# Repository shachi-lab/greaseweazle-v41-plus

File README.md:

# Shachi-lab Greaseweazle V4.1 Plus Board

[🇯🇵 日本語版はこちら](README_ja.md)

This repository contains KiCad design data for a Greaseweazle V4.1 based compatible board created by Shachi-lab.

This board is based on Greaseweazle V4.1, with a few small modifications to make it easier to use with 5.25-inch FDDs and PC-98 style FDD setups.

For convenience, this board is referred to as **V4.1 Plus** in this repository.

**V4.1 Plus is not an official Greaseweazle product name.**

---

## About Greaseweazle

Greaseweazle is an open-source USB floppy interface for reading and writing floppy disks using standard PC floppy disk drives.

Unlike ordinary USB floppy drives, Greaseweazle can access floppy disks at a lower level.  
It can capture and write magnetic flux transitions, which makes it useful for handling disk formats that are not supported by standard USB floppy drives.

For firmware, host tools, usage, and detailed documentation, please refer to the original Greaseweazle project.

* Original Greaseweazle project  
  https://github.com/keirf/greaseweazle

* Greaseweazle Wiki  
  https://github.com/keirf/greaseweazle/wiki

---

## About this repository

This repository provides only the KiCad design data for the Shachi-lab Greaseweazle compatible board.

Firmware, host tools, and usage instructions are not included in this repository.  
This board is a clone-based compatible board, so basic usage follows the original Greaseweazle documentation.

---

## KiCad version

This board design was created with **KiCad 10.0**.

Older versions of KiCad may not open the project correctly.

---

## Board overview

This board is based on Greaseweazle V4.1.

The circuit is close to the original Greaseweazle V4.1 design.  
The board outline, mounting holes, connectors, pin headers, and LED positions are kept as close as possible to the original V4.1 board.

Some parts were changed to make the board easier to hand-assemble and easier to use with 5.25-inch FDDs and PC-98 related FDD setups.

---

## Main differences from the original V4.1 board

* 2-layer PCB
  * The original Greaseweazle V4.1 board is a 4-layer PCB
* SMT parts are mainly 0603 / 1608 size
  * The original board uses 0402 parts
  * This change makes hand assembly easier
* Additional pin headers for PC-98 FDD use
  * These headers are intended for cutting or controlling specific signals
* Additional +12V output path for 5.25-inch FDDs
  * Allows +12V from a common AC adapter to be supplied to a Berg connector

---

## Current status

The board has been tested with a 3.5-inch FDD and a standard DOS/Windows 1.44MB floppy disk.

Confirmed so far:

* Greaseweazle Firmware 1.6 programming
* USB connection on Windows 11
* Recognition with `gw info`
* 3.5-inch FDD connection
* Reading a DOS/Windows 1.44MB floppy disk
* Creating an IMG file using the `ibm.1440` profile
* Opening the IMG file with 7-Zip

The FDD used for this test was `SONY MPF920`.

---

## Not yet confirmed

The following items are still under test.

* Reading PC-98 5.25-inch floppy disks
* Stable operation with 5.25-inch FDDs
* 300rpm / 360rpm related behavior
* DENS signal behavior
* Compatibility with various FDD models

---

## Firmware and usage

Firmware, host tools, and usage follow the original Greaseweazle documentation.

This repository does not include Greaseweazle firmware or host tools.

For this board, the AT32F4 HEX file was used.

Example:

```text
greaseweazle-firmware-at32f4-1.6.hex
```

In my test environment, `gw info` showed the following result.

```text
Host Tools: 1.23
Device:
  Port:     COM7
  Model:    Greaseweazle V4.1
  MCU:      AT32F403A, 216MHz, 224kB SRAM
  Firmware: 1.6
  Serial:   GW053C11222847000007E0A413
  USB:      Full Speed (12 Mbit/s), 128kB Buffer
```

The `Greaseweazle V4.1` model name shown here is returned by the Greaseweazle firmware.  
It does not mean that this board is an official Greaseweazle V4.1 board.

---

## Notes

This is a self-made Greaseweazle compatible board created by Shachi-lab.  
It is not an official Greaseweazle product.

If you build this board, please check the KiCad design data and circuit carefully.  
Use it at your own risk.

Old floppy disks and FDDs may have various mechanical and media-related issues.  
Damaged or dirty floppy disks may cause unstable reading behavior or may contaminate the FDD head.

---

## Related article

Related articles are available on the Shachi-lab blog.

Please note that the blog articles are written in Japanese.

- Greaseweazle category  
  https://blog.shachi-lab.com/category/microcontroller/greaseweazle/
---

## License

This board is based on the original Greaseweazle project by Keir Fraser.

The KiCad design data in this repository is released with respect for the original Greaseweazle project and under the license terms of the original project.

Please refer to the original Greaseweazle repository for license details.

* https://github.com/keirf/greaseweazle

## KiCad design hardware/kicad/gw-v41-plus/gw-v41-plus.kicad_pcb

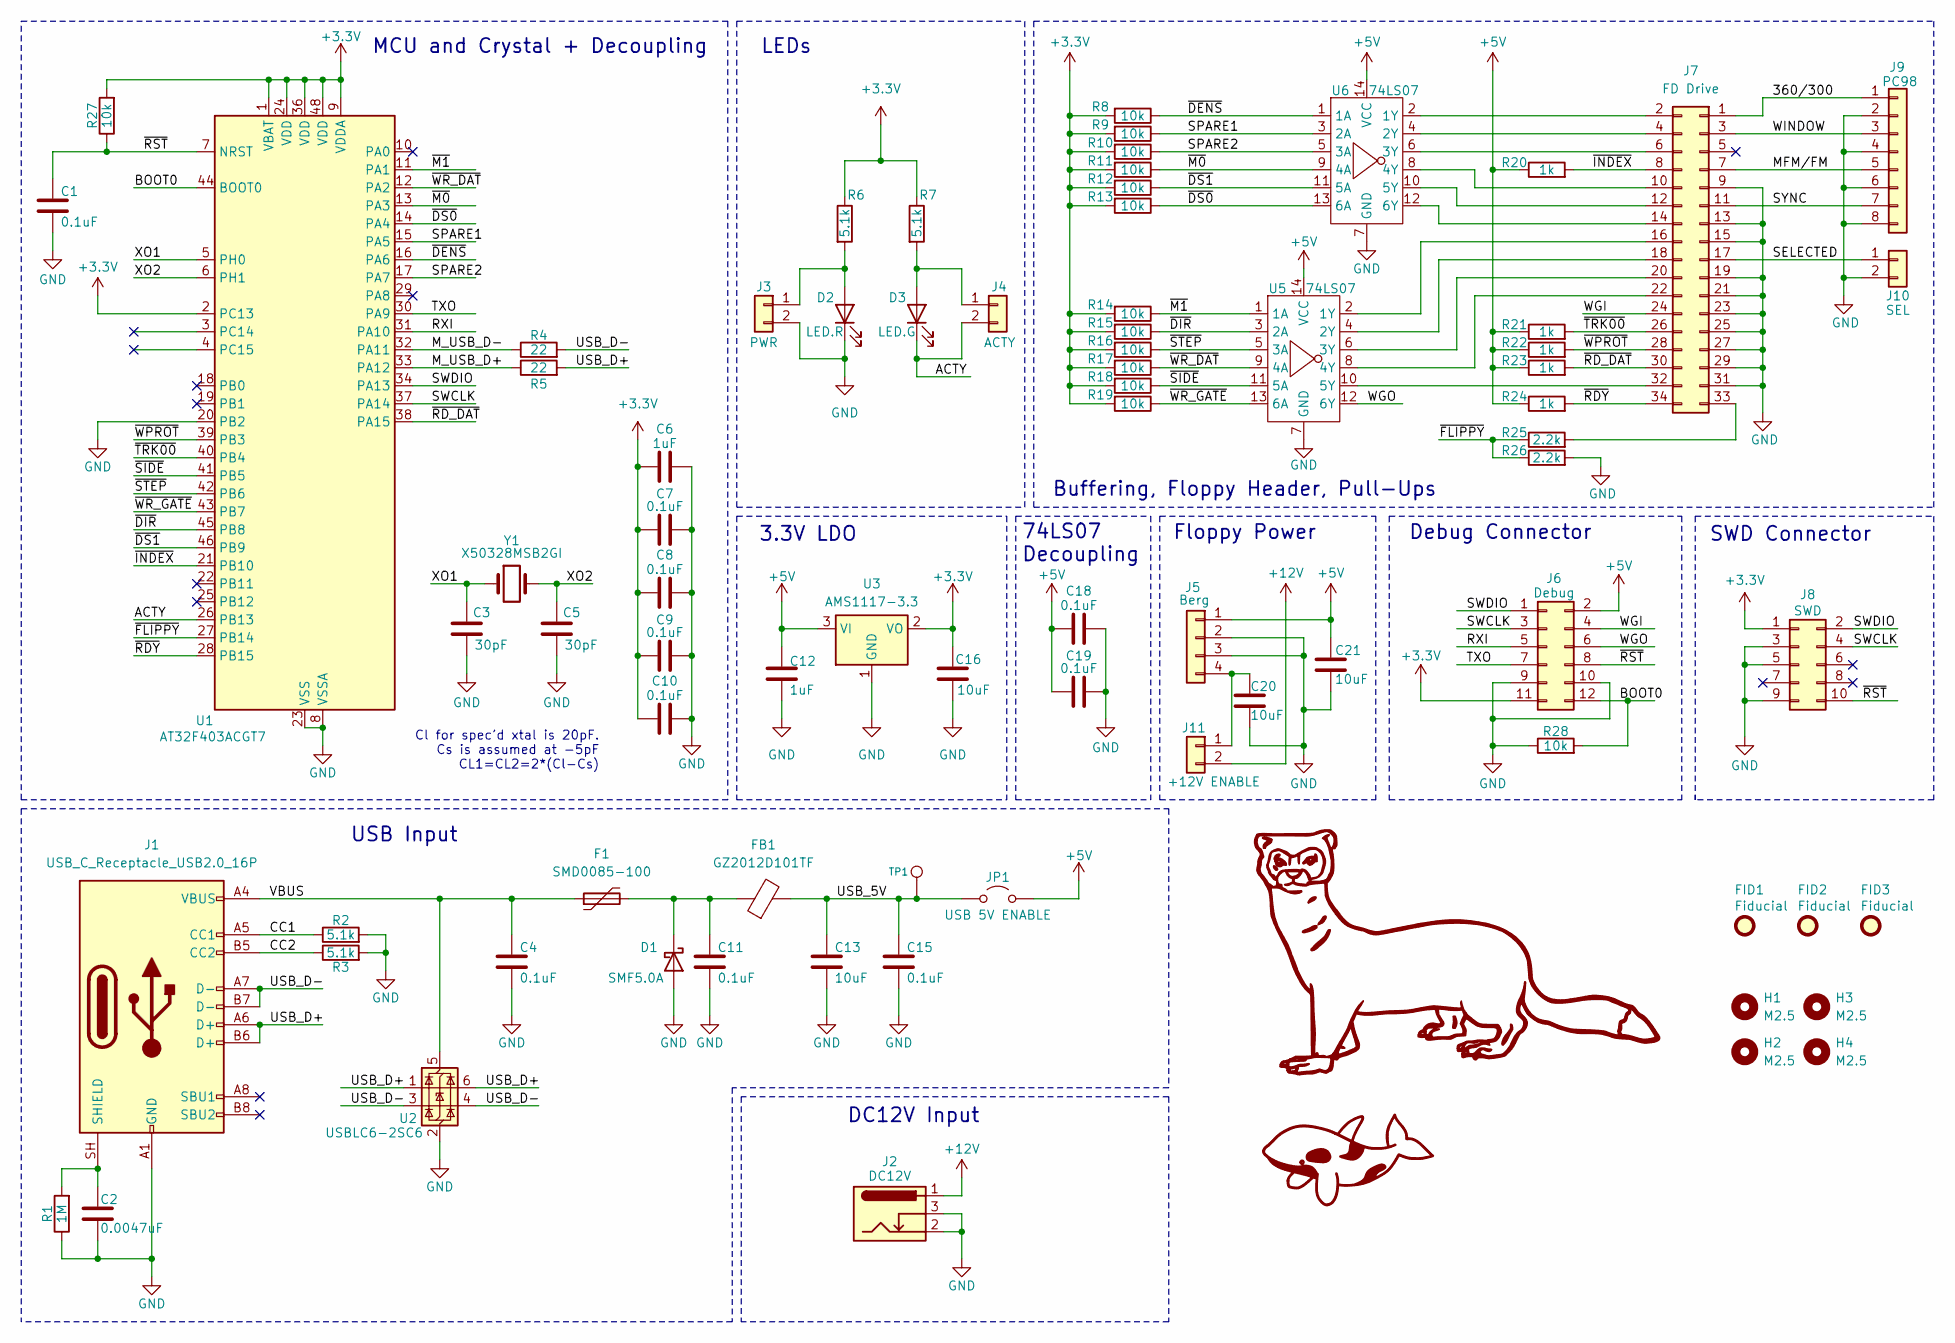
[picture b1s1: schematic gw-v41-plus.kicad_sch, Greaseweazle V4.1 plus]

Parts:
C1, C4, C7, C8, C9, C10, C11, C15, C18, C19: 0.1uF; C_0603_1608Metric
C2: 0.0047uF; C_0603_1608Metric
C3, C5: 30pF; C_0603_1608Metric
C6, C12: 1uF; C_0603_1608Metric
C13, C16, C20, C21: 10uF; C_0805_2012Metric
D1: SMF5.0A; Nexperia_CFP3_SOD-123W
D2: LED.R; LED_0603_1608Metric
D3: LED.G; LED_0603_1608Metric
F1: SMD0085-100; Fuse_1206_3216Metric
FB1: GZ2012D101TF; L_0603_1608Metric
FID1, FID2, FID3: Fiducial; Fiducial_1.5mm_Mask3mm
H1, H2, H3, H4: M2.5; MountingHole_2.7mm_M2.5
J1: USB_C_Receptacle_USB2.0_16P; USB_C_Receptacle_HRO_TYPE-C-31-M-12
J2: DC12V; BarrelJack_Kycon_KLDX-0202-xC_Horizontal
J3: PWR; PinHeader_1x02_P2.54mm_Vertical
J4: ACTY; PinHeader_1x02_P2.54mm_Vertical
J5: Berg; A2540WR-04P1
J6: Debug; PinHeader_2x06_P2.54mm_Vertical
J7: FD Drive; IDC-Header_2x17_P2.54mm_Horizontal
J8: SWD; PinHeader_2x05_P1.27mm_Vertical
J9: PC98; PinHeader_1x08_P2.54mm_Vertical
J10: SEL; PinHeader_1x02_P2.54mm_Vertical
J11: +12V ENABLE; PinHeader_1x02_P2.54mm_Vertical
JP1: USB 5V ENABLE; PinHeader_1x02_P2.54mm_Vertical
R1: 1M; R_0603_1608Metric
R2, R3, R6, R7: 5.1k; R_0603_1608Metric
R4, R5: 22; R_0603_1608Metric
R8, R9, R10, R11, R12, R13, R14, R15, R16, R17, R18, R19, R27, R28: 10k; R_0603_1608Metric
R20, R21, R22, R23, R24: 1k; R_0603_1608Metric
R25, R26: 2.2k; R_0603_1608Metric
TP1: TP; TestPoint_THTPad_1.0x1.0mm_Drill0.5mm
U1: AT32F403ACGT7; LQFP-48_7x7mm_P0.5mm
U2: USBLC6-2SC6; SOT-23-6
U3: AMS1117-3.3; SOT-223-3_TabPin2
U5, U6: 74LS07; SO-14_3.9x8.65mm_P1.27mm
Y1: X50328MSB2GI; Crystal_SMD_5032-2Pin_5.0x3.2mm

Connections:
+3.3V: C6.1, C7.1, C8.1, C9.1, C10.1, C16.1, J6.11, J8.1, R6.1, R7.1, R8.2, R9.2, R10.2, R11.2, R12.2, R13.2, R14.2, R15.2, R16.2, R17.2, R18.2, R19.2, R27.2, U1.1 (VBAT), U1.2 (PC13), U1.9 (VDDA), U1.24 (VDD), U1.36 (VDD), U1.48 (VDD), U3.2 (VO)
+5V: C12.1, C18.1, C19.1, C21.1, J5.1, J6.2, JP1.2 (B), R20.1, R21.1, R22.1, R23.1, R24.1, U3.3 (VI), U5.14 (VCC), U6.14 (VCC)
+12V: J2.1, J11.2
/360/300: J7.1, J9.1
/ACTY: D3.1 (K), J4.2, U1.26 (PB13)
/BOOT0: J6.12, R28.2, U1.44 (BOOT0)
/CC1: J1.A5 (CC1), R2.1
/CC2: J1.B5 (CC2), R3.1
/MFM/FM: J7.7, J9.5
/M_USB_D+: R5.1, U1.33 (PA12)
/M_USB_D-: R4.1, U1.32 (PA11)
/RXI: J6.5, U1.31 (PA10)
/SELECTED: J7.17, J10.1
/SPARE1: R9.1, U1.15 (PA5), U6.3 (2A)
/SPARE2: R10.1, U1.17 (PA7), U6.5 (3A)
/SWCLK: J6.3, J8.4, U1.37 (PA14)
/SWDIO: J6.1, J8.2, U1.34 (PA13)
/SYNC: J7.11, J9.7
/TXO: J6.7, U1.30 (PA9)
/USB_5V: C13.1, C15.1, FB1.2, JP1.1 (A), TP1.1 (1_1)
/USB_D+: J1.A6 (D+), J1.B6 (D+), R5.2, U2.1 (I/O1), U2.6 (I/O1)
/USB_D-: J1.A7 (D-), J1.B7 (D-), R4.2, U2.3 (I/O2), U2.4 (I/O2)
/VBUS: C4.1, F1.1, J1.A4 (VBUS), J1.A9 (VBUS), J1.B4 (VBUS), J1.B9 (VBUS), U2.5 (VBUS)
/WGI: J6.4, J7.24
/WGO: J6.6, U5.12 (6Y)
/WINDOW: J7.3, J9.3
/XO1: C3.1, U1.5 (PH0), Y1.1
/XO2: C5.1, U1.6 (PH1), Y1.2
/~DENS: R8.1, U1.16 (PA6), U6.1 (1A)
/~DIR: R15.1, U1.45 (PB8), U5.3 (2A)
/~DS0: R13.1, U1.14 (PA4), U6.13 (6A)
/~DS1: R12.1, U1.46 (PB9), U6.11 (5A)
/~FLIPPY: R25.1, R26.1, U1.27 (PB14)
/~INDEX: J7.8, R20.2, U1.21 (PB10)
/~M0: R11.1, U1.13 (PA3), U6.9 (4A)
/~M1: R14.1, U1.11 (PA1), U5.1 (1A)
/~RDY: J7.34, R24.2, U1.28 (PB15)
/~RD_DAT: J7.30, R23.2, U1.38 (PA15)
/~RST: C1.1, J6.8, J8.10, R27.1, U1.7 (NRST)
/~SIDE: R18.1, U1.41 (PB5), U5.11 (5A)
/~STEP: R16.1, U1.42 (PB6), U5.5 (3A)
/~TRK00: J7.26, R21.2, U1.40 (PB4)
/~WPROT: J7.28, R22.2, U1.39 (PB3)
/~WR_DAT: R17.1, U1.12 (PA2), U5.9 (4A)
/~WR_GATE: R19.1, U1.43 (PB7), U5.13 (6A)
GND: C1.2, C2.2, C3.2, C4.2, C5.2, C6.2, C7.2, C8.2, C9.2, C10.2, C11.2, C12.2, C13.2, C15.2, C16.2, C18.2, C19.2, C20.2, C21.2, D1.2 (A), D2.1 (K), H2.1, H4.1, J1.A1 (GND), J1.A12 (GND), J1.B1 (GND), J1.B12 (GND), J2.2, J2.3, J3.2, J5.2, J5.3, J6.9, J6.10, J7.9, J7.13, J7.15, J7.19, J7.21, J7.23, J7.25, J7.27, J7.29, J7.31, J8.3, J8.5, J8.9, J9.2, J9.4, J9.6, J9.8, J10.2, R1.1, R2.2, R3.2, R26.2, R28.1, U1.8 (VSSA), U1.20 (PB2), U1.23 (VSS), U1.35 (VSS), U1.47 (VSS), U2.2 (GND), U3.1 (GND), U5.7 (GND), U6.7 (GND); also elsewhere on the board
unnamed: C11.1, D1.1 (K), F1.2, FB1.1
unnamed: D2.2 (A), J3.1, R6.2
unnamed: D3.2 (A), J4.1, R7.2
unnamed: C2.1, J1.SH (SHIELD), R1.2
unnamed: J7.2, U6.2 (1Y)
unnamed: J7.4, U6.4 (2Y)
unnamed: J7.6, U6.6 (3Y)
unnamed: J7.10, U6.8 (4Y)
unnamed: J7.12, U6.10 (5Y)
unnamed: J7.14, U6.12 (6Y)
unnamed: J7.16, U5.2 (1Y)
unnamed: J7.18, U5.4 (2Y)
unnamed: J7.20, U5.6 (3Y)
unnamed: J7.22, U5.8 (4Y)
unnamed: J7.32, U5.10 (5Y)
unnamed: J7.33, R25.2
unnamed: C20.1, J5.4, J11.1

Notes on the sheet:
MCU and Crystal + Decoupling
USB Input
74LS07 Decoupling
Debug Connector
Floppy Power
3.3V LDO
SWD Connector
Cl for spec'd xtal is 20pF. Cs is assumed at -5pF CL1=CL2=2*(Cl-Cs)
LEDs
Buffering, Floppy Header, Pull-Ups
DC12V Input

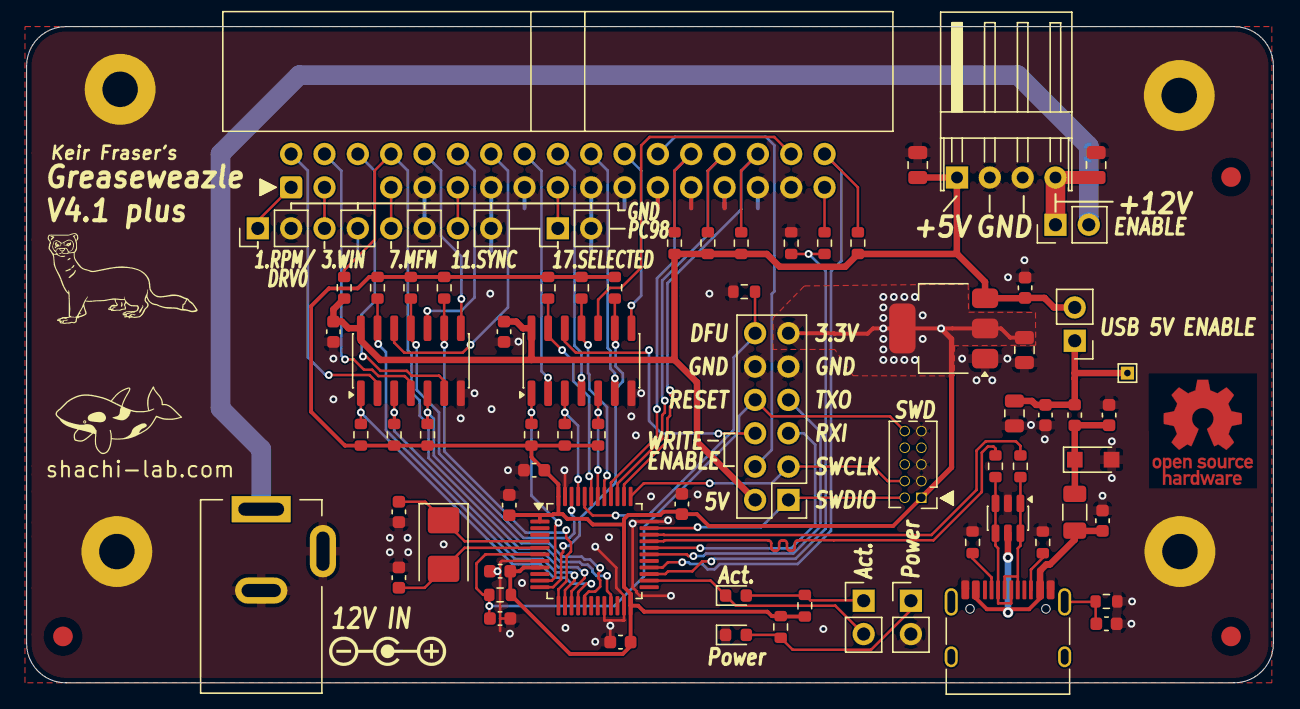
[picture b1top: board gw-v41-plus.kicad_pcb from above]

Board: 2 copper layers, 95.0 x 50.0 mm, 83 parts (1 on the bottom side), 63 nets.

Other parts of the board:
H1#2, H3#2: M2.5; MountingHole_2.7mm_M2.5_Pad
H2#2, H4#2: M2.5; MountingHole_2.7mm_M2.5
kibuzzard-6A2215D5: G***; kibuzzard-6A2215D5

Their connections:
GND: H1#2.1, H3#2.1; also elsewhere on the board

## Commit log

2026-06-26 Initial KiCad design files
